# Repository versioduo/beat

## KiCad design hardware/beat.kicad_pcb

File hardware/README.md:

# beat
🧲 4 Channel Solenoid Controller

## Schematic
[PDF](beat.pdf)

## Bill Of Materials
[Interactive BOM](https://html-preview.github.io/?url=https://github.com/versioduo/beat/main/hardware-beat-bom.html)

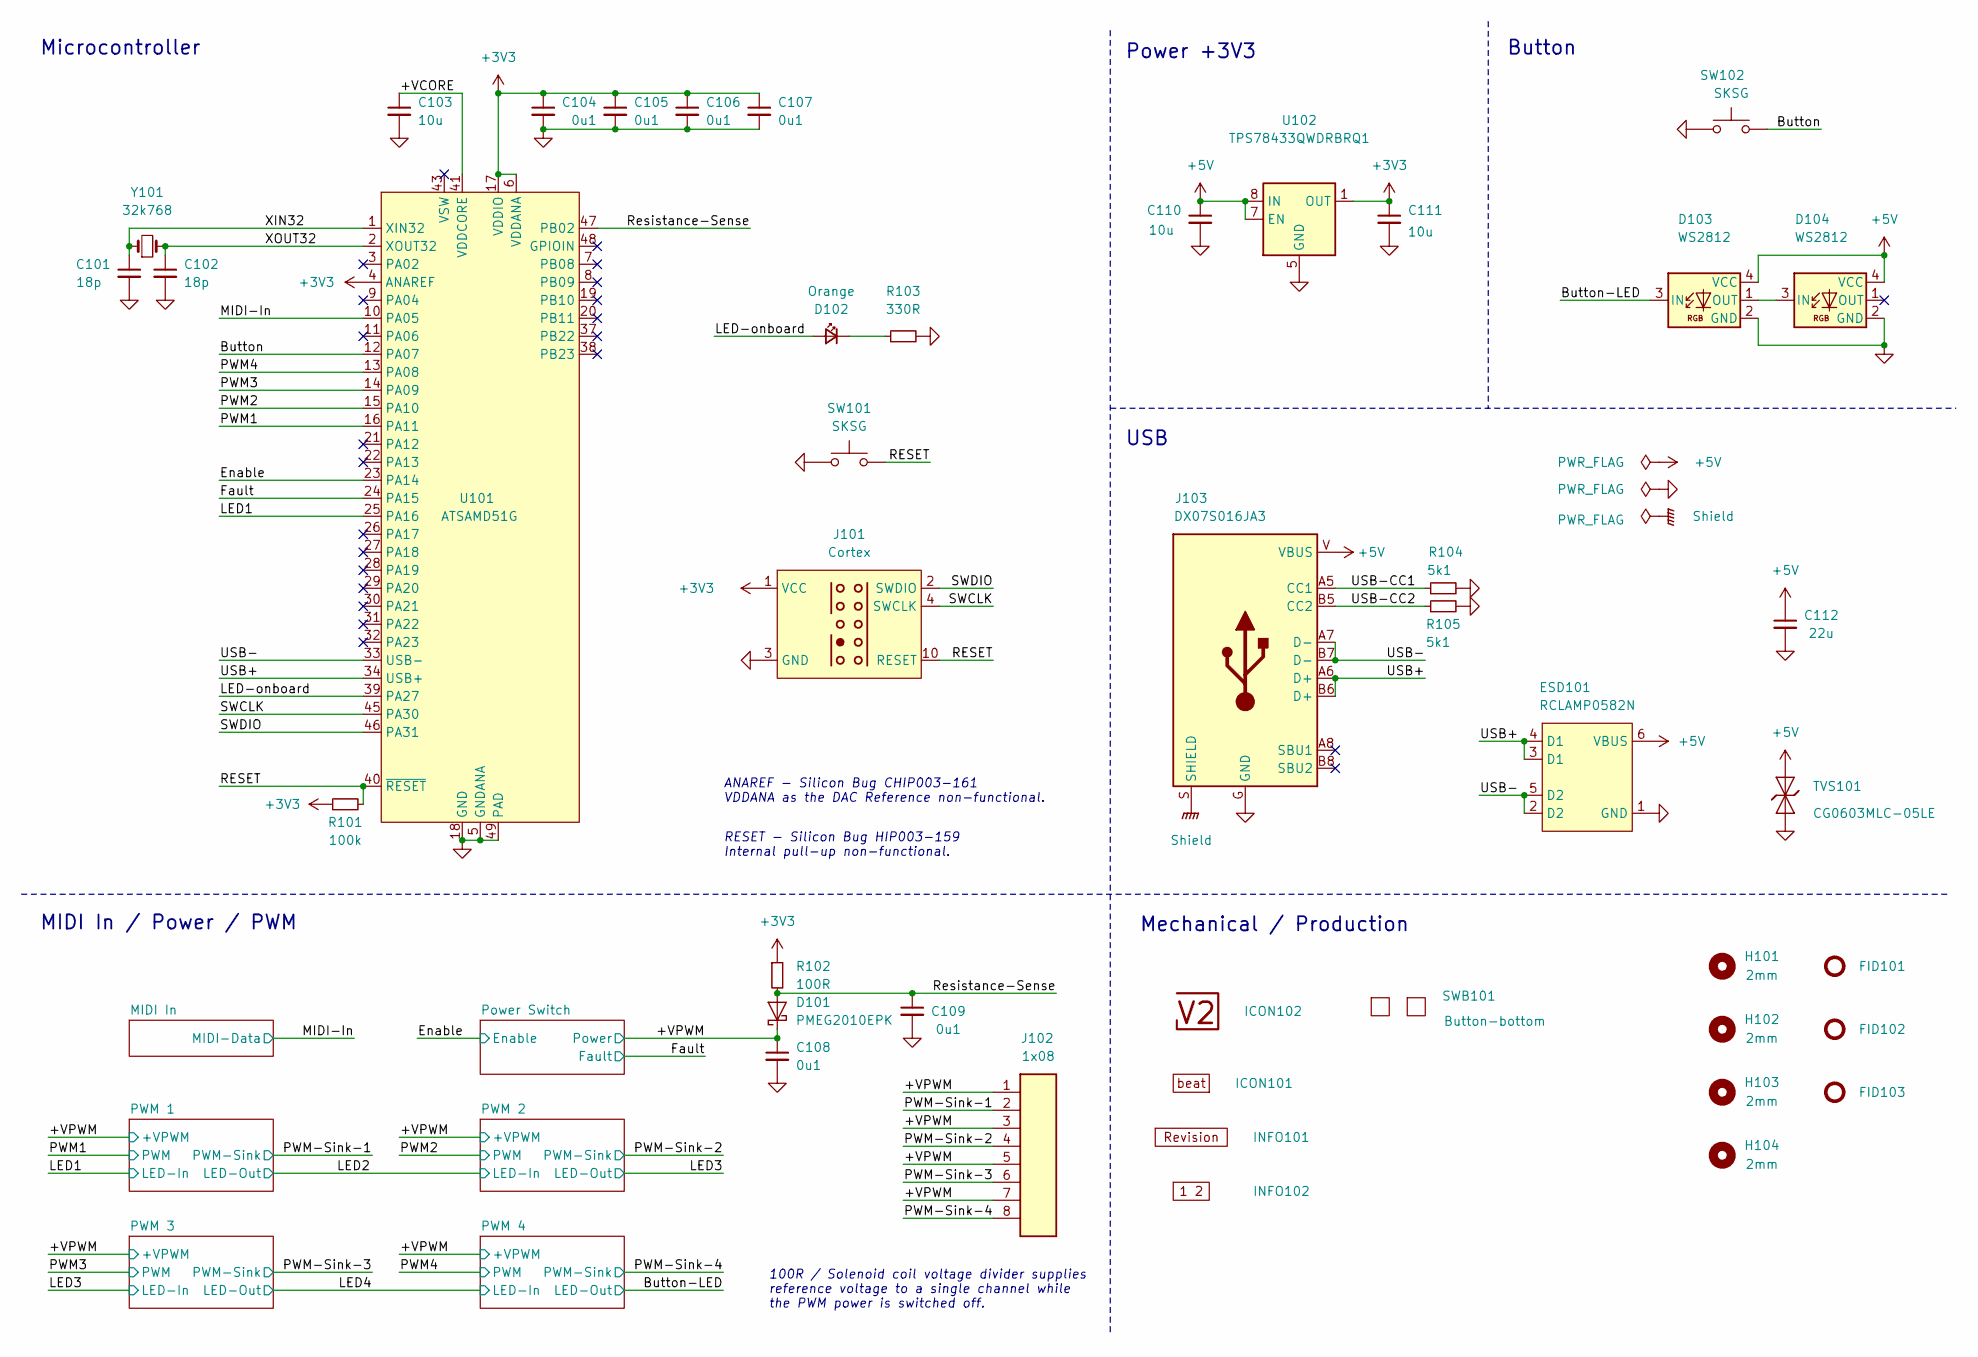
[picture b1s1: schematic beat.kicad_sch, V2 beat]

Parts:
C101, C102: 18p; C_1608; Rating 50V; Mouser 810-CGA3E2C0G1H180J
C103: 10u; C_1608; Rating 10V; Mouser 810-C1608X6S1A106M
C104, C105, C106, C107, C108, C109: 0u1; C_1608; Rating 50V; Mouser 810-CGA3E2X7R1H104MA
C110, C111: 10u; C_2012; Rating 25V; Mouser 810-C2012X5R1E106K
C112: 22u; C_3225; Rating 25V; Mouser 810-CGA6P3X7R1E226M5
D101: PMEG2010EPK; D_SOD-1608; Rating 20V; Mouser 771-PMEG2010EPK
D102: Orange; LED_1608; Rating 605nm; Mouser 755-SML-D12D1WT86
D103, D104: WS2812; WS2812-2020; Rating 15mA; LCSC C965555
ESD101: RCLAMP0582N; SLP1210N6; Rating 20kV; Mouser 947-RCLAMP0582N.TCT
FID101, FID102, FID103: Fiducial_Paste; Fiducial_0.5mm_Mask1mm_Paste
H101, H102, H103, H104: 2mm; MountingHole_2mm
ICON101: Board_axis; Board_beat_Small
ICON102: V2-logo; Logo_Small
INFO101: Revision
INFO102: Layer_Numbers-4
J101: Cortex
J102: 1x08; SocketHeader_1x08_P2.54mm_Horizontal
J103: DX07S016JA3; JAE_DX07S016JA3; Rating USB2.0; Mouser 656-DX07S016JA3R1500
R101: 100k; R_1608; Rating 100mW; Mouser 71-CRCW0603100KFKEAC
R102: 100R; R_1608; Rating 330mW; Mouser 71-CRCW0603100RFKEAH
R103: 330R; R_1608; Rating 100mW; Mouser 71-CRCW0603330RFKEAC
R104, R105: 5k1; R_1608; Rating 100mW; Mouser 71-CRCW06035K10FKEAC
SW101, SW102: SKSG; Rating 1.6N; Mouser 688-SKSGACE010
SWB101: Button-bottom; PCB_Button-bottom
TVS101: CG0603MLC-05LE; D_1608; Rating 5V; Mouser 652-CG0603MLC-05LE
U101: ATSAMD51G; QFN-48-1EP_7x7mm_P0.5mm_EP5.45x5.45mm_ThermalVias; Rating Cortex-M4F; Mouser 556-ATSAMD51G19AMU
U102: TPS78433QWDRBRQ1; VSON-8-1_3x3mm_P0.65_EP1.65x2.4mm; Rating 300mA; Mouser 595-TPS78433QWDRBRQ1
Y101: 32k768; Crystal_SMD_3215-2Pin_3.2x1.5mm; Rating 10ppm; Mouser 815-ABS0716632.768KT

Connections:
+3V3: C104.1, C105.1, C106.1, C107.1, C111.1, J101.1 (VCC), R101.1, R102.1, U101.4 (ANAREF), U101.6 (VDDANA), U101.17 (VDDIO), U101.36 (VDDIO), U101.44 (VDDIO), U102.1 (OUT); also elsewhere on the board
+5V: C110.1, C112.1, D103.4 (VCC), D104.4 (VCC), ESD101.6 (VBUS), J103.V (VBUS), TVS101.2 (A), U102.6 (EN), U102.7 (EN), U102.8 (IN); also elsewhere on the board
/+VCORE: C103.1, U101.41 (VDDCORE)
/+VPWM: C108.1, D101.1 (K), J102.1, J102.3, J102.5, J102.7; also elsewhere on the board
/Button: SW102.2, U101.12 (PA07)
/Button-LED: D103.3 (IN); also elsewhere on the board
/Enable: U101.23 (PA14); also elsewhere on the board
/Fault: U101.24 (PA15); also elsewhere on the board
/LED1: U101.25 (PA16); also elsewhere on the board
/LED-onboard: D102.2 (A), U101.39 (PA27)
/MIDI-In: U101.10 (PA05); also elsewhere on the board
/PWM1: U101.16 (PA11); also elsewhere on the board
/PWM2: U101.15 (PA10); also elsewhere on the board
/PWM3: U101.14 (PA09); also elsewhere on the board
/PWM4: U101.13 (PA08); also elsewhere on the board
/PWM-Sink-1: J102.2; also elsewhere on the board
/PWM-Sink-2: J102.4; also elsewhere on the board
/PWM-Sink-3: J102.6; also elsewhere on the board
/PWM-Sink-4: J102.8; also elsewhere on the board
/RESET: J101.10 (RESET), R101.2, SW101.2, U101.40 (~RESET)
/Resistance-Sense: C109.1, D101.2 (A), R102.2, U101.47 (PB02)
/SWCLK: J101.4 (SWCLK), U101.45 (PA30)
/SWDIO: J101.2 (SWDIO), U101.46 (PA31)
/Shield: J103.S (SHIELD)
/USB+: ESD101.3 (D1), ESD101.4 (D1), J103.A6 (D+), J103.B6 (D+), U101.34 (USB+)
/USB-: ESD101.2 (D2), ESD101.5 (D2), J103.A7 (D-), J103.B7 (D-), U101.33 (USB-)
/USB-CC1: J103.A5 (CC1), R104.1
/USB-CC2: J103.B5 (CC2), R105.1
/XIN32: C101.1, U101.1 (XIN32), Y101.1
/XOUT32: C102.1, U101.2 (XOUT32), Y101.2
GND: C101.2, C102.2, C103.2, C104.2, C105.2, C106.2, C107.2, C108.2, C109.2, C110.2, C111.2, C112.2, D103.2 (GND), D104.2 (GND), ESD101.1 (GND), J101.3 (GND), J101.5 (GND), J103.G (GND), R103.2, R104.2, R105.2, SW101.1, SW102.1, TVS101.1 (K), U101.5 (GNDANA), U101.18 (GND), U101.35 (GND), U101.42 (GND), U101.49 (PAD), U102.5 (GND), U102.9 (GND); also elsewhere on the board
unnamed: D102.1 (K), R103.1
unnamed: D103.1 (OUT), D104.3 (IN)

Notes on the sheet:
ANAREF - ﻿Silicon Bug CHIP003-161 VDDANA as the DAC Reference non-functional.
MIDI In / Power / PWM
RESET - ﻿Silicon Bug HIP003-159 Internal pull-up non-functional.
Button
100R / Solenoid coil voltage divider supplies reference voltage to a single channel while the PWM power is switched off.
Power +3V3
Mechanical / Production
Microcontroller
USB

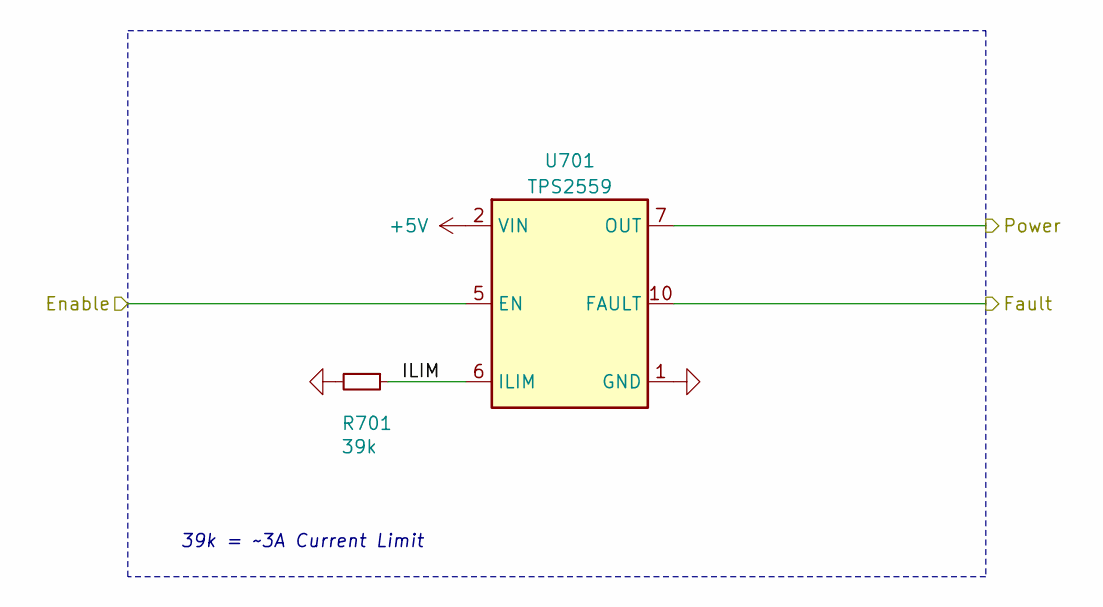
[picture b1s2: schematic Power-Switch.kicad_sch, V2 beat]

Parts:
R701: 39k; R_1608; Rating 500mW; Mouser 71-RCS060339K0FKEA
U701: TPS2559; VSON-10-1EP_3x3mm_P0.5mm_EP1.65x2.4mm_ThermalVias; Rating 4.7A; Mouser 595-TPS2559DRCR

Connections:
+5V: U701.2 (VIN), U701.3 (VIN), U701.4 (VIN); also elsewhere on the board
/+VPWM: U701.7 (OUT), U701.8 (OUT), U701.9 (OUT); also elsewhere on the board
/Enable: U701.5 (EN); also elsewhere on the board
/Fault: U701.10 (FAULT); also elsewhere on the board
/Power Switch/ILIM: R701.1, U701.6 (ILIM)
GND: R701.2, U701.1 (GND), U701.11 (GND); also elsewhere on the board

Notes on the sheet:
39k = ~3A Current Limit

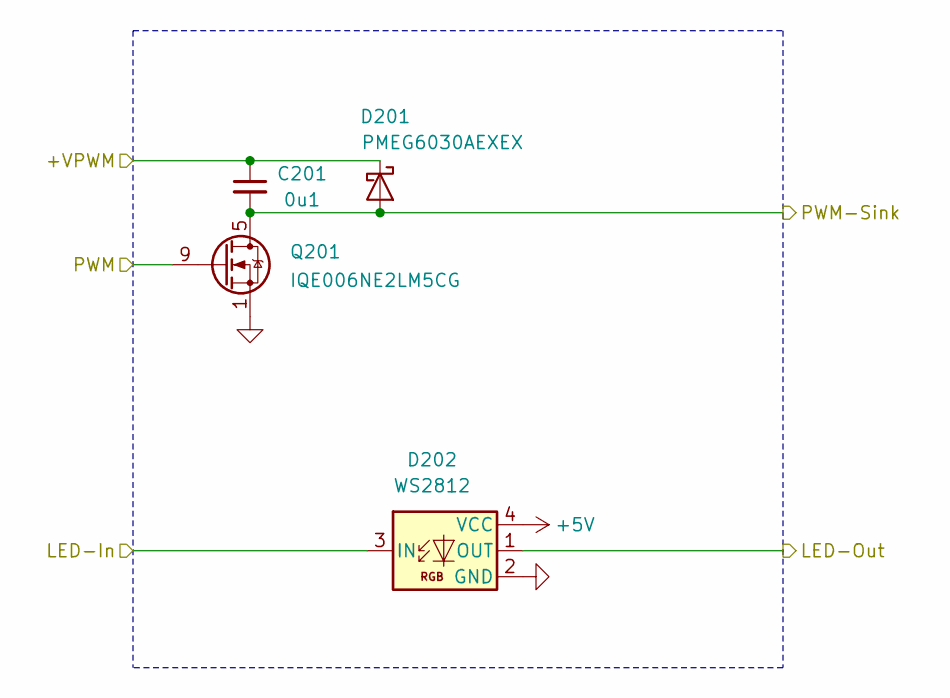
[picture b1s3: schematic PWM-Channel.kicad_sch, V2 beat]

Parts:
C201: 0u1; C_1608; Rating 50V; Mouser 810-CGA3E2X7R1H104MA
D201: PMEG6030AEXEX; D_SOD-123HP; Rating 60V; Mouser 771-PMEG6030AEXEX
D202: WS2812; WS2812-2020; Rating 15mA; LCSC C965555
Q201: IQE006NE2LM5CG; WHTFN-9; Rating 25V; Mouser 726-IQE006NE2LM5CGAT

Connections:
+5V: D202.4 (VCC); also elsewhere on the board
/+VPWM: C201.1, D201.1 (K); also elsewhere on the board
/LED1: D202.3 (IN); also elsewhere on the board
/LED2: D202.1 (OUT); also elsewhere on the board
/PWM1: Q201.9 (G); also elsewhere on the board
/PWM-Sink-1: C201.2, D201.2 (A), Q201.5 (D); also elsewhere on the board
GND: D202.2 (GND), Q201.1 (S); also elsewhere on the board

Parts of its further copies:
C301, C401, C501: 0u1; C_1608; Rating 50V; Mouser 810-CGA3E2X7R1H104MA
D301, D401, D501: PMEG6030AEXEX; D_SOD-123HP; Rating 60V; Mouser 771-PMEG6030AEXEX
D302, D402, D502: WS2812; WS2812-2020; Rating 15mA; LCSC C965555
Q301, Q401, Q501: IQE006NE2LM5CG; WHTFN-9; Rating 25V; Mouser 726-IQE006NE2LM5CGAT

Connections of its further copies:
+5V: D302.4 (VCC), D402.4 (VCC), D502.4 (VCC); also elsewhere on the board
/+VPWM: C301.1, C401.1, C501.1, D301.1 (K), D401.1 (K), D501.1 (K); also elsewhere on the board
/Button-LED: D502.1 (OUT); also elsewhere on the board
/LED2: D302.3 (IN); also elsewhere on the board
/LED3: D302.1 (OUT), D402.3 (IN)
/LED4: D402.1 (OUT), D502.3 (IN)
/PWM2: Q301.9 (G); also elsewhere on the board
/PWM3: Q401.9 (G); also elsewhere on the board
/PWM4: Q501.9 (G); also elsewhere on the board
/PWM-Sink-2: C301.2, D301.2 (A), Q301.5 (D); also elsewhere on the board
/PWM-Sink-3: C401.2, D401.2 (A), Q401.5 (D); also elsewhere on the board
/PWM-Sink-4: C501.2, D501.2 (A), Q501.5 (D); also elsewhere on the board
GND: D302.2 (GND), D402.2 (GND), D502.2 (GND), Q301.1 (S), Q401.1 (S), Q501.1 (S); also elsewhere on the board

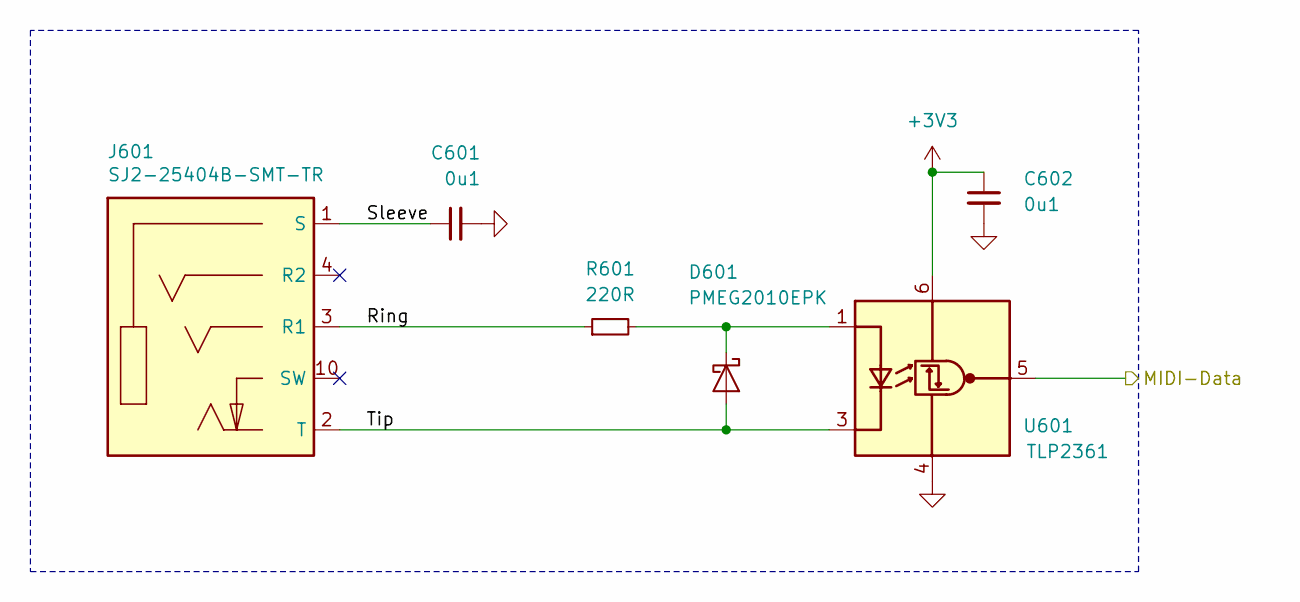
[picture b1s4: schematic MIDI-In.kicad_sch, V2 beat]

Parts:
C601, C602: 0u1; C_1608; Rating 50V; Mouser 810-CGA3E2X7R1H104MA
D601: PMEG2010EPK; D_SOD-1608; Rating 20V; Mouser 771-PMEG2010EPK
J601: SJ2-25404B-SMT-TR; CUI_SJ2-25404B-SMT-TR; Rating 2.5mm; Mouser 490-SJ2-25404BSMT-TR
R601: 220R; R_1608; Rating 333mW; Mouser 667-ERJ-PA3F2200V
U601: TLP2361; SO-5-6_4.55x3.7mm_P1.27mm; Rating 15Mbps; Mouser 757-TLP2361TPRE

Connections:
+3V3: C602.1, U601.6 (VDD); also elsewhere on the board
/MIDI In/Ring: J601.3 (R1), R601.1
/MIDI In/Sleeve: C601.1, J601.1 (S)
/MIDI In/Tip: D601.2 (A), J601.2 (T), U601.3 (K)
/MIDI-In: U601.5 (VO); also elsewhere on the board
GND: C601.2, C602.2, U601.4 (GND); also elsewhere on the board
unnamed: D601.1 (K), R601.2, U601.1 (A)

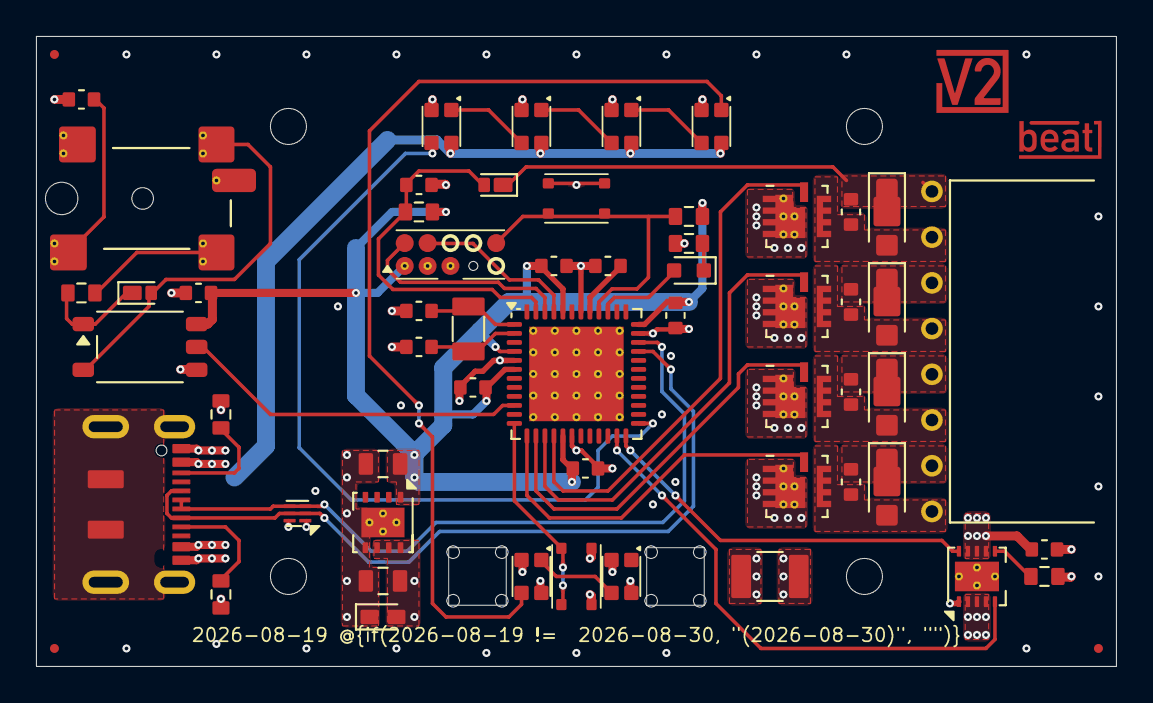
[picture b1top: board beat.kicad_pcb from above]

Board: 4 copper layers, 60.0 x 35.0 mm, 67 parts (0 on the bottom side), 40 nets.

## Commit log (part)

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2025-12-29 Import
2025-12-29 Colour
2026-01-15 Refresh
2026-02-01 Update library
2026-02-10 Use date as revision
2026-02-13 Replace Order_Number
2026-03-11 Replace diode
2026-03-14 Update ESD suppressor
2026-05-11 Good Bye Imperial
2026-06-23 Update V2MIDI API
